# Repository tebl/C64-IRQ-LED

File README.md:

# C64 IRQ LED
I was looking for something similar to the Amigas Bifrost-module, but for the Commodore 64 since that is the machine that is closest to my 8-bit heart. Looking around I found an [article](https://www.nightfallcrew.com/04/03/2011/commodore-64-irq-bicolor-led/) with a snippet from an old dutch magazine (complete copy [here](https://github.com/tebl/C64-IRQ-LED/blob/main/gallery/resetknop.jpg)), it uses a dual-colour LED that changes colour depending on the status of the IRQ-line. What that means is that when the Commodore 64 is accessing I/O devices such as system ROMs, cartridge or disk systems the power LED will change to green - and back to red again, when finished. Exciting stuff!

## Build and install
Most of the construction is straight forward, just follow the BOM below as well as the notices where you need to make a few decisions. Do I need or want to bother with a switch? Does my RGB LED work?

Connector J2 is there so you can use an SPDT-switch to disable the LED module, ensuring it will always stay red. According to discussions I've seen, it might get irritating when using things such as GEOS because *everything* uses an IRQ, so if you do - consider wiring up one to these pins. If you do not need it, solder a piece of wire across pins 1-2.

You need to get a common cathode (*CC*) LED with more than one colour, ideally a dual colour one like in the original article. Personally I just cut off the blue pin on a *CC* RGB, then used that though the effect is better with frosted LEDs instead of the clear ones. **Don't** solder it into place until you've test-fitted it for length in place inside your C64 case, solder everything else instead.

Next step is to buy another breadbin-style Commodore 64, because you probably deserve one! Then, remove old power LED and save it in a drawer somewhere (or sell it on ebay as a *"rare"* spare part). Hopefully some bedroom engineer haven't glued the thing in there - in my case it was rubberized glue so that fell apart decades ago. The newer RGB LED might be a tight fit for the existing LED mount though it should fit - just apply some pressure on the front to snap it into place. Afterwards, add the module on top - it might stay on there by itself. if it doesn't you'll need to add some double-sided tape to the IC. Now you can probably solder the LED legs into place permanently - just take care not to melt your case!

The last piece of the puzzle is attaching the whole thing to the C64 motherboard, you can refer to the picture above as this is where I added the three wires needed (white wire is for [Stereo SID](https://github.com/tebl/C64-Stereo-SID) board). I'm using a cut-off set of female dupont wires, the easiest is to wire them to the cartridge port and matching the female part of it to the **markings on the board** (pin order has been changed). Looking at the cartridge port as pictured above: 
- Pin 1, the blue wire, goes to GND (J1 pin 1)
- Pin 3, the green wire, goes to VCC (J1 pin 2)
- Pin 4, the yellow wire, goes to IRQ (J1 pin 3)

Before powering up, double-check that GND and VCC is in the correct spot, swapping them around will kill the IC on the IRQ LED board. Enjoy your freqeuently green power LED!

# BOM
Most parts should be easy to get a hold of from your favourite local electronic component shop, but since I don't have access to the more serious ones I'm mostly getting my components from ebay/AliExpress (free shipping most places, but plan on waiting 3-4 weeks though).

| Reference    | Item                                  | Count |
| ------------ | ------------------------------------- | ----- |
| PCB          | Fabricate using Gerber files ([order](https://www.pcbway.com/project/shareproject/Commodore_64_IRQ_LED.html))  |     1 |
| D1 *         | 5mm Bi-colour LED (common cathode)    |     1 |
| J1           | 3-pin right-angle header pins         |     1 |
| J2 **        | Piece of wire                         |     1 |
| R1,R2        | 330 ohm resistor                      |     2 | 
| U1           | 74LS04 or 74HCT04 (DIP-14)            |     1 |

*) These are 3 pin LEDs of the common cathode variety, check using diode test on a multimeter to ensure that the center pin is GND and that you know which colour goes where. Alternatively, jam a CR2032 battery between the pins. Common cathode RGB LED can be used, just cut off the blue one.

**) You can wire a 3-pin SPDT wire into these pins as a means to enable/disable the mod, solder a piece of leftover wire between pins 1-2 to enable it permanently (if you do not want a switch).

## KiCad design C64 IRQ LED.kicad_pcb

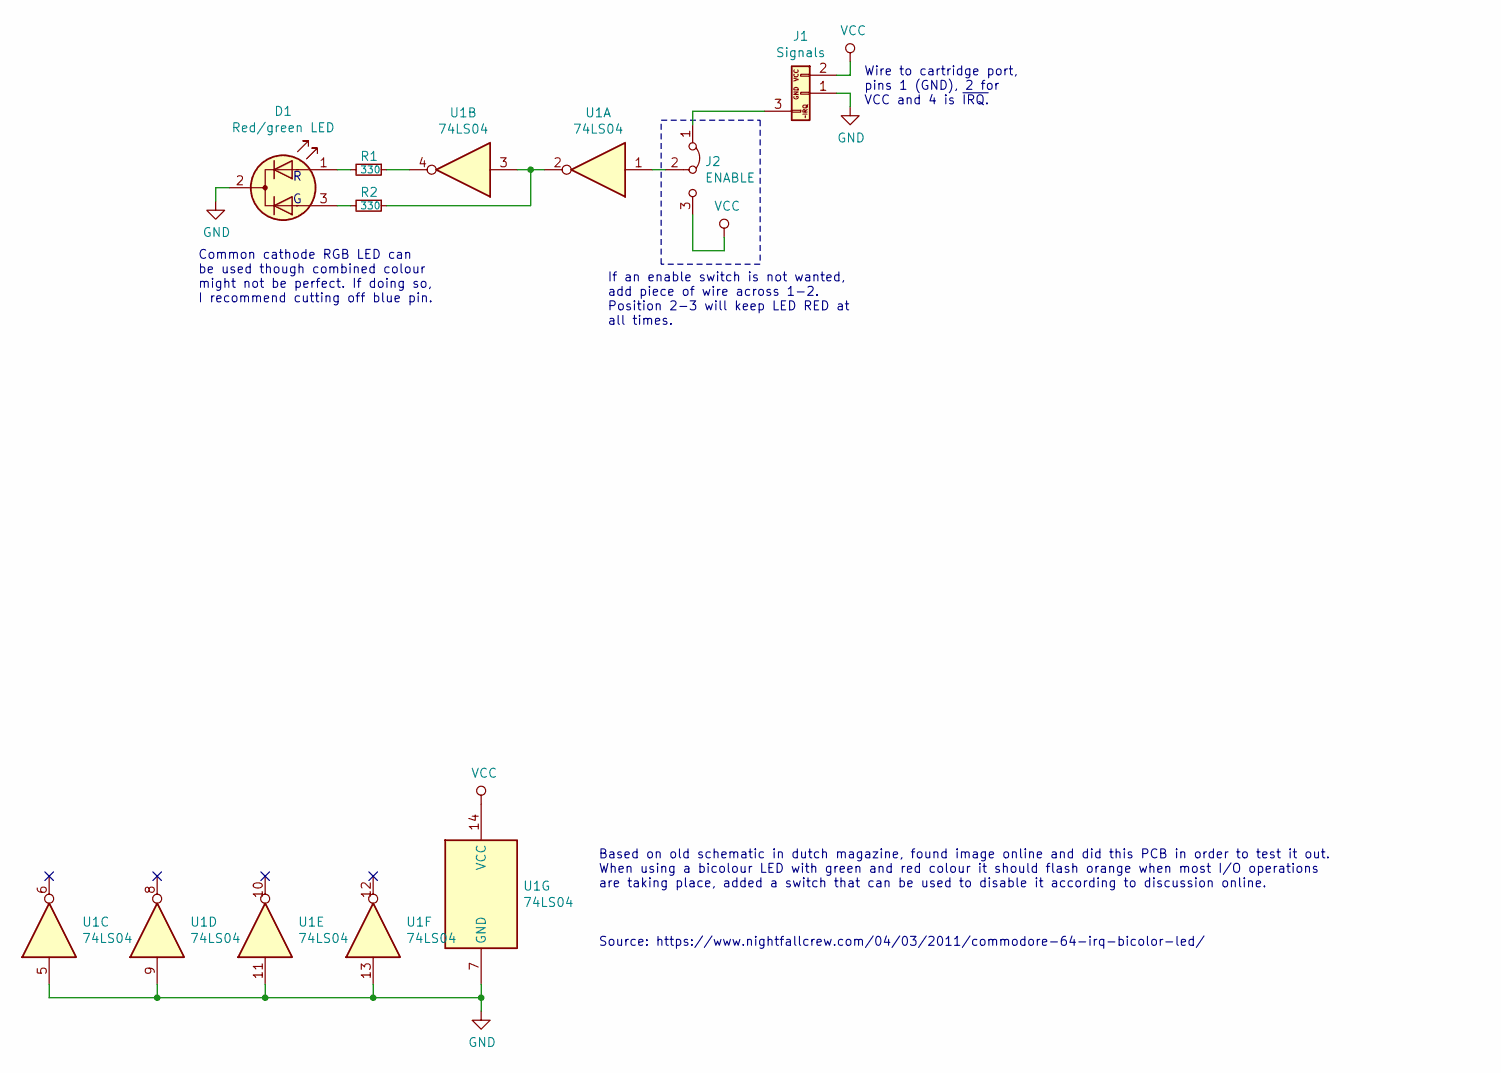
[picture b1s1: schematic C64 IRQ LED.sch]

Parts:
D1: Red/green LED; LED_D5.0mm-3
J1: Signals; Pin_Header_Angled_1x03_Pitch2.54mm
J2: ENABLE; Pin_Header_Straight_1x03_Pitch2.54mm
R1, R2: 330; R_Axial_DIN0207_L6.3mm_D2.5mm_P10.16mm_Horizontal
U1: 74LS04; DIP-14_W7.62mm_LongPads

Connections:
GND: D1.2 (K), J1.1 (GND), U1.5, U1.7 (GND), U1.9, U1.11, U1.13
unnamed: D1.1 (A1), R1.2
unnamed: D1.3 (A2), R2.2
unnamed: J1.3, J2.1 (A)
unnamed: J2.2 (C), U1.1
unnamed: R1.1, U1.4
unnamed: R2.1, U1.2, U1.3
VCC: J1.2 (VCC), J2.3 (B), U1.14 (VCC)

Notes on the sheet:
Based on old schematic in dutch magazine, found image online and did this PCB in order to test it out. When using a bicolour LED with green and red colour it should flash orange when most I/O operations are taking place, added a switch that can be used to disable it according to discussion online.
Source: https://www.nightfallcrew.com/04/03/2011/commodore-64-irq-bicolor-led/
Wire to cartridge port, pins 1 (GND), 2 for VCC and 4 is ~IRQ.
If an enable switch is not wanted, add piece of wire across 1-2. Position 2-3 will keep LED RED at all times.
Common cathode RGB LED can be used though combined colour might not be perfect. If doing so, I recommend cutting off blue pin.

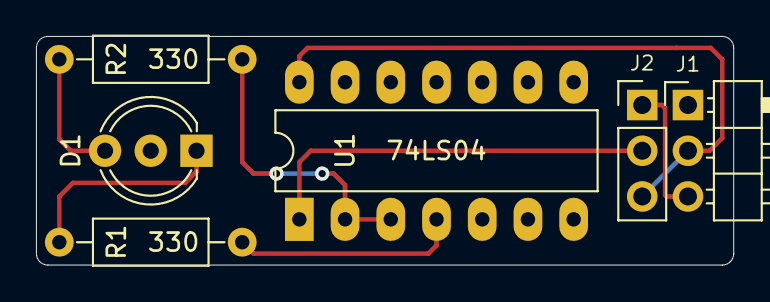
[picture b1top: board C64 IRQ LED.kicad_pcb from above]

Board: 2 copper layers, 38.7 x 12.7 mm, 6 parts (0 on the bottom side), 8 nets.

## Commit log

2020-10-17 Basic schematic
2020-10-17 Gerber expor
2020-10-17 Added README
2020-11-21 Changed pin order to match expansion port
2020-11-21 Formatting
